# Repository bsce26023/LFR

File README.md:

# Autonomous Line Following Robot

I designed a LFR from scratch including the PCBs for main board and a custom sensor array. I designed this because I saw a friend of mine going into robotics competetions, so I also wanted to participate in them but I didn't have a robot that I could take to those competetions, so I finally built one myself. I chose STM32 because in some of those events there is a requirement that your robot should not have wireless connectivity, so the first thing that came into my mind was arduino uno but it is very slow and basic compared to other microcontrollers available on market then after some research I had two options Raspberry Pi Pico RP2040 or a STM32 Black Pill. raspberry pi pico had only 3 analog pins so I went with STM32.

To View the 3D assembly -->  [Assembly](https://cad.onshape.com/documents/d45a99fa843b34be3d8e85fd/w/9a64eb3e4a0355d274d4a744/e/07efc429ec569cf6f0da1301?renderMode=0&uiState=6a73ae4ff920c2919cbadd91)

||||
| :---: | :---: | :---: |
|  |  |  |

# Components

I've decided the components based on affordability, speed, availability and ease of use.
Starting with the micro controller I've selected **STM 32 BlackPill** and for motors I've selected **3000rpm 6v N20 motors with encoders** for fast speed  to drive these motors I've chosen **TB6612FNG motor driver** because it has low voltage drop and also it is way lighter than L298N. I've decided to use a 2S Li-Po battery which is about 7.4v which can power the motors with ease and to power STM32 I'd use a step down buck converter to convert these 7.4v into 5v so we don't damage the STM32 to charge the battery I'd use a 2S charger and for the sensors I've designed a custom sensor array.

##  PCB and Connections

To talk about the connections, I'd Start with the Power connections. The battery provides 7.4v which goes to VMOT pin of motor driver and buck converter. the buck converter then outputs 5v which goes to VSYS on Pico. Now we have 3 voltages. i.e. 7.4v, 5v and 3.3v. now the 3.3v goes to VCC and STBY pin of TB6612FNG and VCC pin on Sensor Array. 
Now lets talk about the Data and Logic Signals. The GPIO pins from 0 to 18 will be connected to sensor array and GPIO pins 19,20, 21, 22, 26, 27 will be connected to PWMA, AIN1, AIN2, PWMB, BIN1 and BIN2 respectively.
At the end the AO1,  AO2 and BO1, BO2 will be connected to left and right motors respectively.
[]

|Schematics|Tracks|
| :---: | :---: |
|  |  |

## Custom Built Sensor Array

I designed the schematics for the sensor array, it is the working principle is inspired from the QTR-16RC sensor array. I designed this because traditional sensors and sensor arrays look too uncool, so I had to design something that looked aesthetic and visually pleasing.

|Schematics|Tracks|
| :---: | :---: |
|  |  |

## Assembly & Firmware Guide

Because STM32 boards lack native USB bootloaders out-of-the-box like standard Arduino boards, flashing firmware requires a specific procedure using either an **ST-LINK V2 programmer** or the **built-in UART system memory bootloader**. 

### Step 1: Mechanical & Electrical Assembly
1. **Chassis & Motors:** Secure the DC gear motors to the mechanical chassis frame and attach the wheels.
2. **PCB Mounting:** Mount the fabricated PCB securely onto the chassis using standoffs.
3. **Wiring Connections:**
   * Connect the motor output leads from the gear motors to the motor driver output terminals (`M1`, `M2`).
   * Connect the IR sensor array to the designated analog/digital input header pins on the PCB.
   * Wire the power distribution, ensuring proper fusing and a stable common ground between the logic circuitry and motor drivers.

### Step 2: Setting Up the Development Environment
1. Install **Visual Studio Code** with the **PlatformIO IDE** extension (recommended for STM32 development) or **Arduino IDE** with the STMSS/STM32 Cores by STMicroelectronics installed via the Board Manager.
2. Clone or download this repository to your local machine.

### Step 3: Connecting the Programmer (ST-LINK V2 Method)
To flash code to an STM32 board, wire an external **ST-LINK V2 programmer** to the board's SWD pins:

| ST-LINK V2 Pin | STM32 Target Pin | Function |
| :--- | :--- | :--- |
| **3.3V** | **3.3V** | Power Supply |
| **GND** | **GND** | Common Ground |
| **SWDIO** | **PA13 (DIO)** | Serial Wire Data |
| **SWCLK** | **PA14 (CLK)** | Serial Wire Clock |

*Note: Ensure the target board is powered either via the ST-LINK's 3.3V pin (if current draw is low) or via an independent battery/bench supply.*

### Step 4: Uploading the Firmware
1. Open the project workspace in your IDE.
2. Verify that your `platformio.ini` or Arduino board settings match your exact STM32 part number (e.g., `stm32f103c8`).
3. Build/compile the project to check for syntax or dependency errors.
4. Initiate the upload command:
   * **In PlatformIO:** Click the **Upload** arrow icon (PlatformIO will automatically invoke OpenOCD and interface with your ST-LINK).
   * **In Arduino IDE:** Select **ST-LINK** under *Tools > Programmer*, then click **Upload**.
5. Once the upload finishes successfully, disconnect the programmer (or keep it connected for serial debugging via UART if configured), power cycle the robot, and place it on the test track.

# Bill of Materials (BOM)

| Name | Purpose | Quantity | Total Cost (USD) | Link | Distributor |
| --- | --- | --- | --- | --- | --- |
| PCB | PCB | 2 | 17 | https://cart.jlcpcb.com/shopcart/cart/ | JLCPCB |
| Mounting Brackets | Mounting motors | 1 | 3 | https://a.aliexpress.com/_c41oltrB | AliExpress |
| N20 Wheels | Wheels for Motors | 4 | 10 | https://a.aliexpress.com/_c3mDdjNx | Ali Express |
| Caster Wheels | Caster wheels | 2 | 4 | https://a.aliexpress.com/_c2yFCmMd | AliExpress |
| Slide Switch | Power Switch | 1 | 2 | https://a.aliexpress.com/_c3g6KmzX | AliExpress |
| TB6612FNG | Motor Driver | 1 | 4 | https://a.aliexpress.com/_c3bzgEgz | AliExpress |
| N20 Motors | Motors with Encoders | 4 | 25 | https://a.aliexpress.com/_c39Rykzn | AliExpress |
| Capacitor | Capacitance | 1 | 3 | https://a.aliexpress.com/_c3Ig4r1X | Aliexpress |
| Resistors | Resistance | 2 | 5 | https://a.aliexpress.com/_c3G1MsVL | Aliexpress |
| Limit switch | Bump sensor | 1 | 2.5 | https://a.aliexpress.com/_c3uz2Isv | Aliexpress |
| Ultrasonic sensor | Measures distance | 1 | 6 | https://a.aliexpress.com/_c35Zat1R | Aliexpress |
| TCRT5000 | Sensor | 1 | 7 | https://a.aliexpress.com/_c3RbgmiN | Aliexpress |
| Header pins | Soldering on pcb | 2 | 4 | https://a.aliexpress.com/_c4B0APx7 | Aliexpress |
| Mp1584 | Buck converter | 1 | 4.5 | https://a.aliexpress.com/_c4qnSguh | Aliexpress |
| Charging module | For charging battery | 1 | 2 | https://a.aliexpress.com/_c3Dtj3BL | Aliexpress |
| STM32 | Microcontroller | 1 | 6 | https://a.aliexpress.com/_c3GJD5FF | Aliexpress |
| Soldering Iron | For Soldering | 1 | 15 | https://epro.pk/product/soldering-iron-station-adjustable-temperature-esd-safe-kada-936-in-pakistan/ | Epro |
| Customs | - | - | 60 | - | AliExpress |
| Shipping | - | - | 20 | - | JLCPCB |
|  |  |  |  |  |  |
| Total | - | - | 200 | - | - |

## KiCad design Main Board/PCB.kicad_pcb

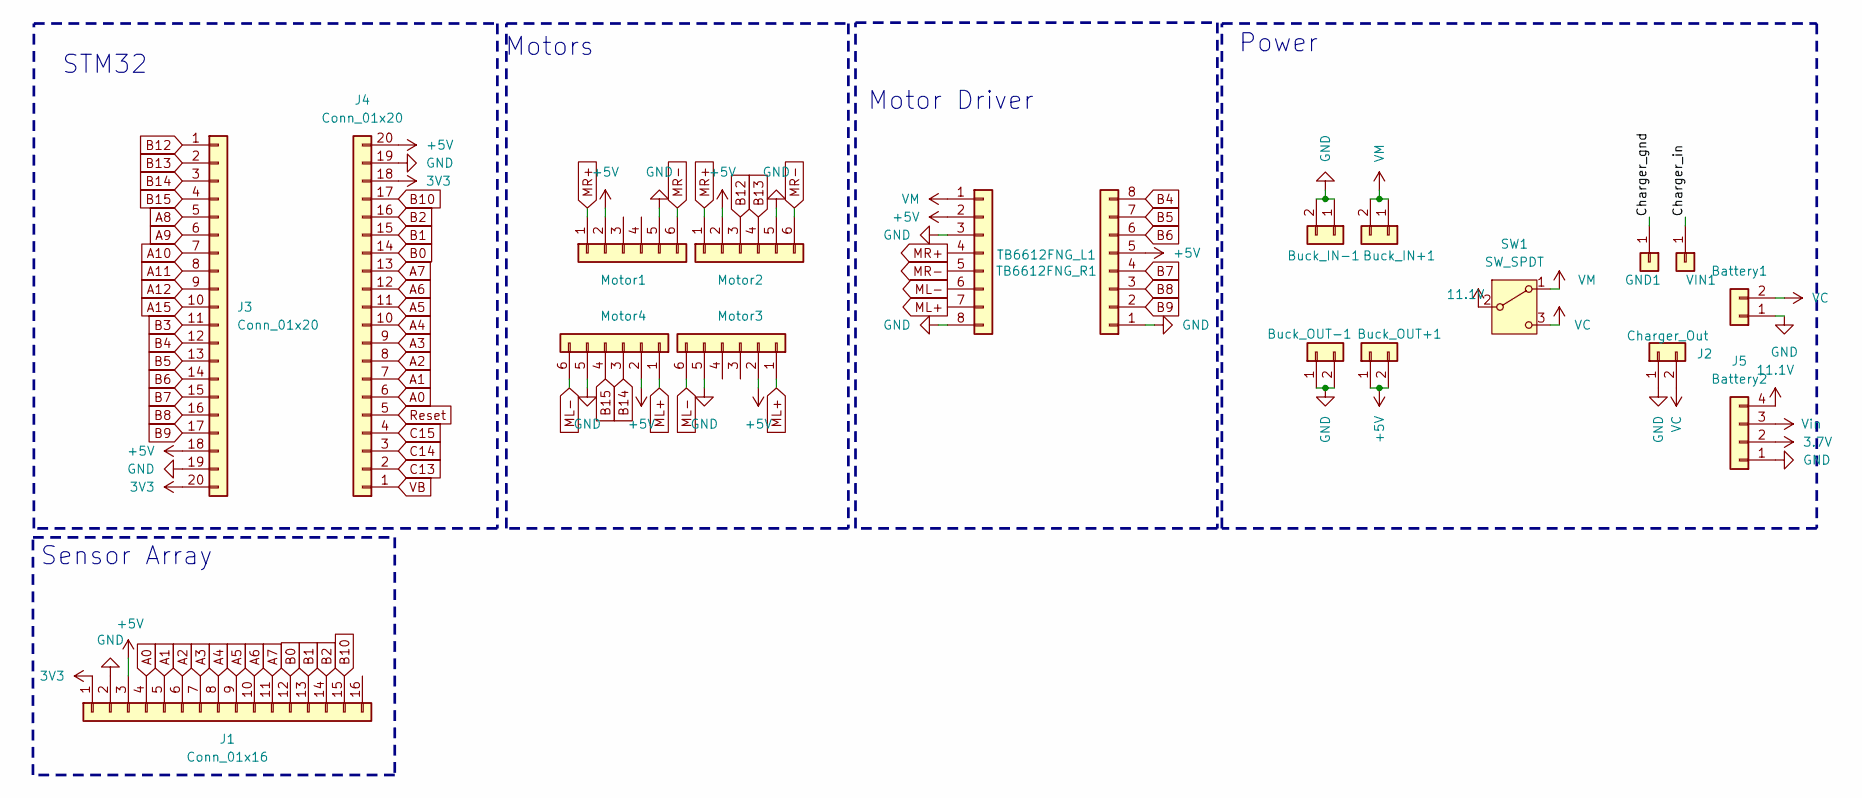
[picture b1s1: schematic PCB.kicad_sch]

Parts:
Battery1: Conn_01x02; AMASS_XT60-M_1x02_P7.20mm_Vertical
Buck_IN+1: Conn_01x02; PinSocket_1x02_P2.54mm_Vertical
Buck_IN-1: Conn_01x02; PinSocket_1x02_P2.54mm_Vertical
Buck_OUT+1: Conn_01x02; PinSocket_1x02_P2.54mm_Vertical
Buck_OUT-1: Conn_01x02; PinSocket_1x02_P2.54mm_Vertical
GND1: Conn_01x01; PinSocket_1x01_P2.54mm_Vertical
J1: Conn_01x16; PinHeader_1x16_P2.54mm_Vertical
J2: Charger_Out; PinSocket_1x02_P2.54mm_Vertical
J3, J4: Conn_01x20; PinSocket_1x20_P2.54mm_Vertical
J5: Battery2; JST_XH_B4B-XH-A_1x04_P2.50mm_Vertical
Motor1, Motor2, Motor3, Motor4: Conn_01x06; PinSocket_1x06_P2.54mm_Vertical
SW1: SW_SPDT; SW_Slide_SP3T_Straight_CK_OS103012MU1QP1
TB6612FNG_L1, TB6612FNG_R1: Conn_01x08; PinHeader_1x08_P2.54mm_Vertical
VIN1: Conn_01x01; PinHeader_1x01_P2.54mm_Vertical

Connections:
3.7V: J5.2
3V3: J1.1, J3.20, J4.18
+5V: Buck_OUT+1.1, Buck_OUT+1.2, J1.3, J3.18, J4.20, Motor1.2, Motor2.2, Motor3.2, Motor4.2, TB6612FNG_L1.2, TB6612FNG_R1.5
/Charger_gnd: GND1.1
/Charger_in: VIN1.1
A0: J1.4, J4.6
A1: J1.5, J4.7
A2: J1.6, J4.8
A3: J1.7, J4.9
A4: J1.8, J4.10
A5: J1.9, J4.11
A6: J1.10, J4.12
A7: J1.11, J4.13
A8: J3.5
A9: J3.6
A10: J3.7
A11: J3.8
A12: J3.9
A15: J3.10
B0: J1.12, J4.14
B1: J1.13, J4.15
B2: J1.14, J4.16
B3: J3.11
B4: J3.12, TB6612FNG_R1.8
B5: J3.13, TB6612FNG_R1.7
B6: J3.14, TB6612FNG_R1.6
B7: J3.15, TB6612FNG_R1.4
B8: J3.16, TB6612FNG_R1.3
B9: J3.17, TB6612FNG_R1.2
B10: J1.15, J4.17
B12: J3.1, Motor2.3
B13: J3.2, Motor2.4
B14: J3.3, Motor4.3
B15: J3.4, Motor4.4
C13: J4.2
C14: J4.3
C15: J4.4
GND: Battery1.1, Buck_IN-1.1, Buck_IN-1.2, Buck_OUT-1.1, Buck_OUT-1.2, J1.2, J2.1, J3.19, J4.19, J5.1, Motor1.5, Motor2.5, Motor3.5, Motor4.5, TB6612FNG_L1.3, TB6612FNG_L1.8, TB6612FNG_R1.1
ML+: Motor3.1, Motor4.1, TB6612FNG_L1.7
ML-: Motor3.6, Motor4.6, TB6612FNG_L1.6
MR+: Motor1.1, Motor2.1, TB6612FNG_L1.4
MR-: Motor1.6, Motor2.6, TB6612FNG_L1.5
Reset: J4.5
VB: J4.1
VM: Buck_IN+1.1, Buck_IN+1.2, SW1.1 (A), TB6612FNG_L1.1
Vin: J5.3

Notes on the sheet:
Power
Motor Driver
STM32
Motors
Sensor Array

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
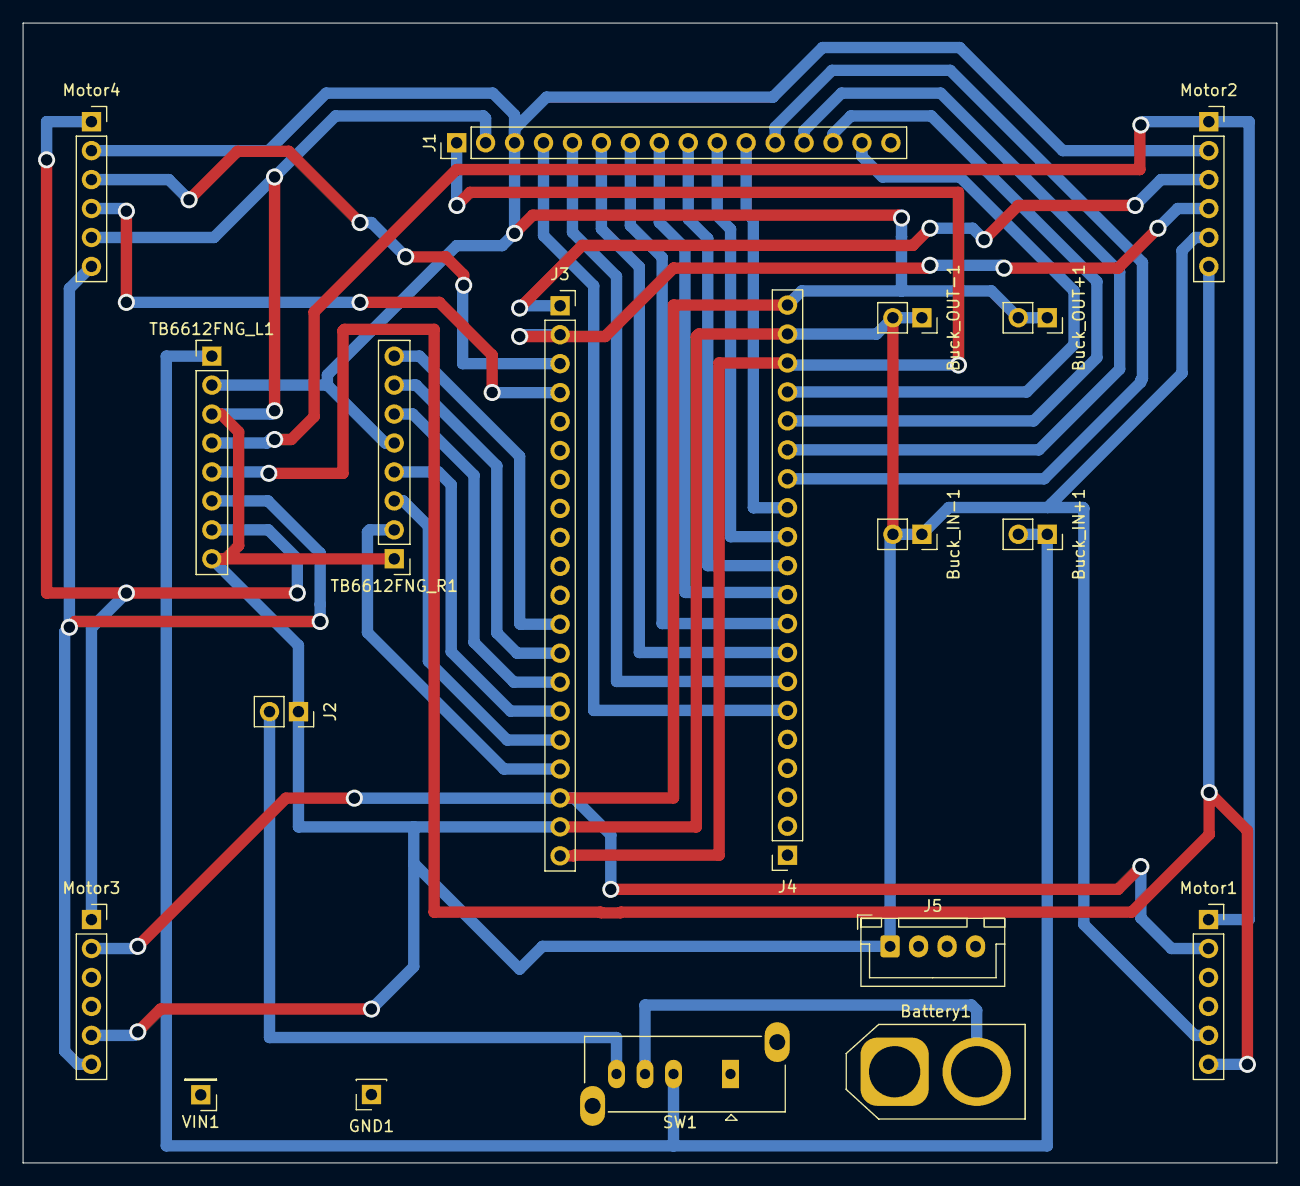
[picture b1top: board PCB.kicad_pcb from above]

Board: 2 copper layers, 110.0 x 100.0 mm, 19 parts (0 on the bottom side), 32 nets.

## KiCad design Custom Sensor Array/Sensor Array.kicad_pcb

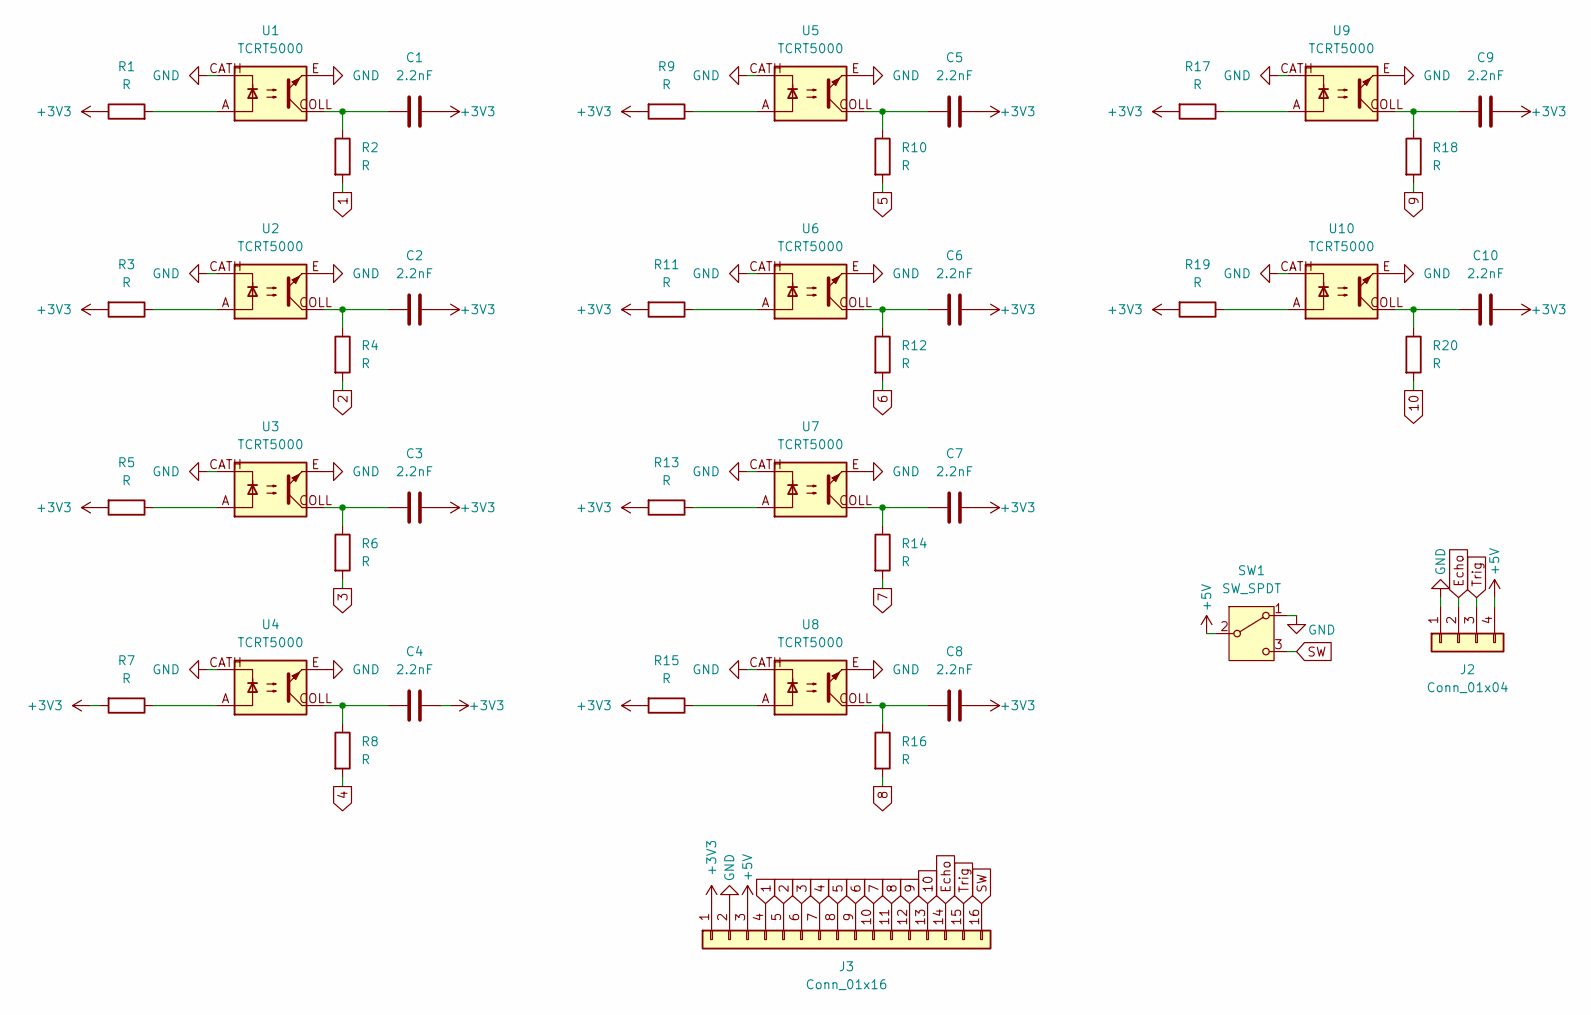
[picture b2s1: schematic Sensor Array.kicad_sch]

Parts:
C1, C2, C3, C4, C5, C6, C7, C8, C9, C10: 2.2nF; C_0805_2012Metric_Pad1.18x1.45mm_HandSolder
J2: Conn_01x04; PinHeader_1x04_P2.54mm_Vertical
J3: Conn_01x16; PinHeader_1x16_P2.54mm_Vertical
R1, R2, R3, R4, R5, R6, R7, R8, R9, R10, R11, R12, R13, R14, R15, R16, R17, R18, R19, R20: R; R_0805_2012Metric_Pad1.20x1.40mm_HandSolder
SW1: SW_SPDT; SW_Slide_SPDT_Straight_CK_OS102011MS2Q
U1, U2, U3, U4, U5, U6, U7, U8, U9, U10: TCRT5000; tcrt5000

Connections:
1: J3.4, R2.2
2: J3.5, R4.2
3: J3.6, R6.2
4: J3.7, R8.2
5: J3.8, R10.2
6: J3.9, R12.2
7: J3.10, R14.2
8: J3.11, R16.2
9: J3.12, R18.2
10: J3.13, R20.2
+3V3: C1.2, C2.2, C3.2, C4.2, C5.2, C6.2, C7.2, C8.2, C9.2, C10.2, J3.1, R1.1, R3.2, R5.2, R7.2, R9.2, R11.2, R13.2, R15.2, R17.2, R19.2
+5V: J2.4, J3.3, SW1.2 (B)
Echo: J2.2, J3.14
GND: J2.1, J3.2, SW1.1 (A), U1.CATH, U1.E, U2.CATH, U2.E, U3.CATH, U3.E, U4.CATH, U4.E, U5.CATH, U5.E, U6.CATH, U6.E, U7.CATH, U7.E, U8.CATH, U8.E, U9.CATH, U9.E, U10.CATH, U10.E
unnamed: C1.1, R2.1, U1.COLL
unnamed: C2.1, R4.1, U2.COLL
unnamed: C3.1, R6.1, U3.COLL
unnamed: C4.1, R8.1, U4.COLL
unnamed: C5.1, R10.1, U5.COLL
unnamed: C6.1, R12.1, U6.COLL
unnamed: C7.1, R14.1, U7.COLL
unnamed: C8.1, R16.1, U8.COLL
unnamed: C9.1, R18.1, U9.COLL
unnamed: C10.1, R20.1, U10.COLL
unnamed: R1.2, U1.A
unnamed: R3.1, U2.A
unnamed: R5.1, U3.A
unnamed: R7.1, U4.A
unnamed: R9.1, U5.A
unnamed: R11.1, U6.A
unnamed: R13.1, U7.A
unnamed: R15.1, U8.A
unnamed: R17.1, U9.A
unnamed: R19.1, U10.A
SW: J3.16, SW1.3 (C)
Trig: J2.3, J3.15

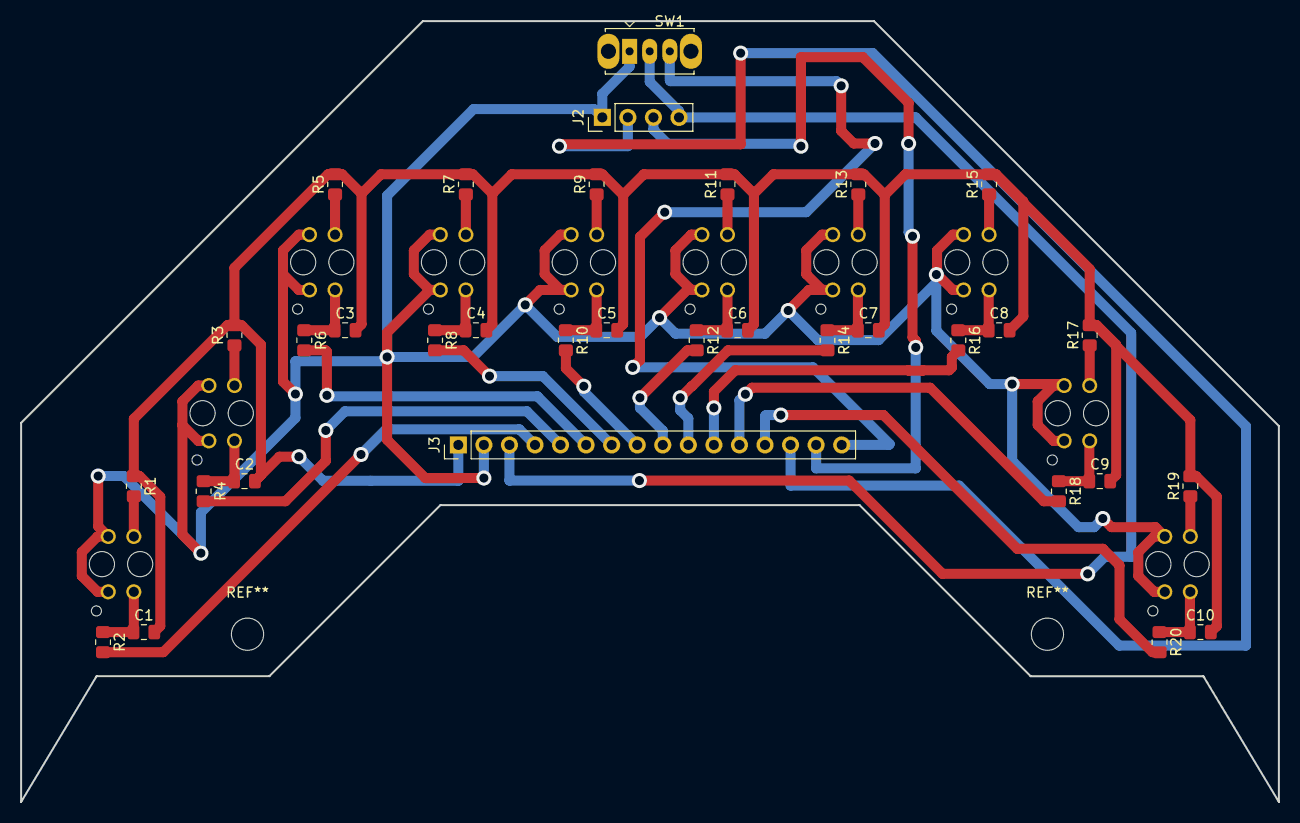
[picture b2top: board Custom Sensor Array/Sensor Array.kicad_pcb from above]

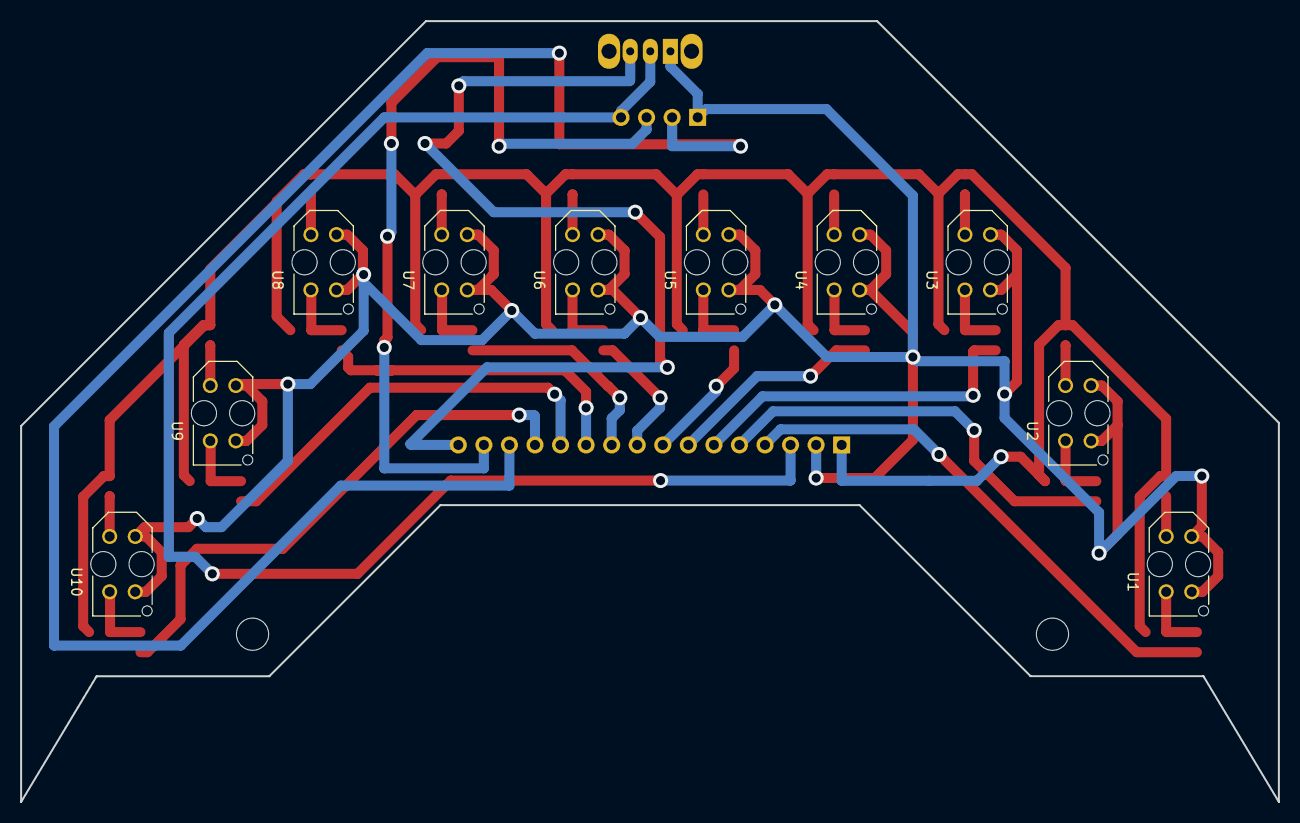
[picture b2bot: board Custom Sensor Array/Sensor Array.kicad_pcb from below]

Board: 2 copper layers, 125.0 x 77.6 mm, 43 parts (10 on the bottom side), 36 nets.

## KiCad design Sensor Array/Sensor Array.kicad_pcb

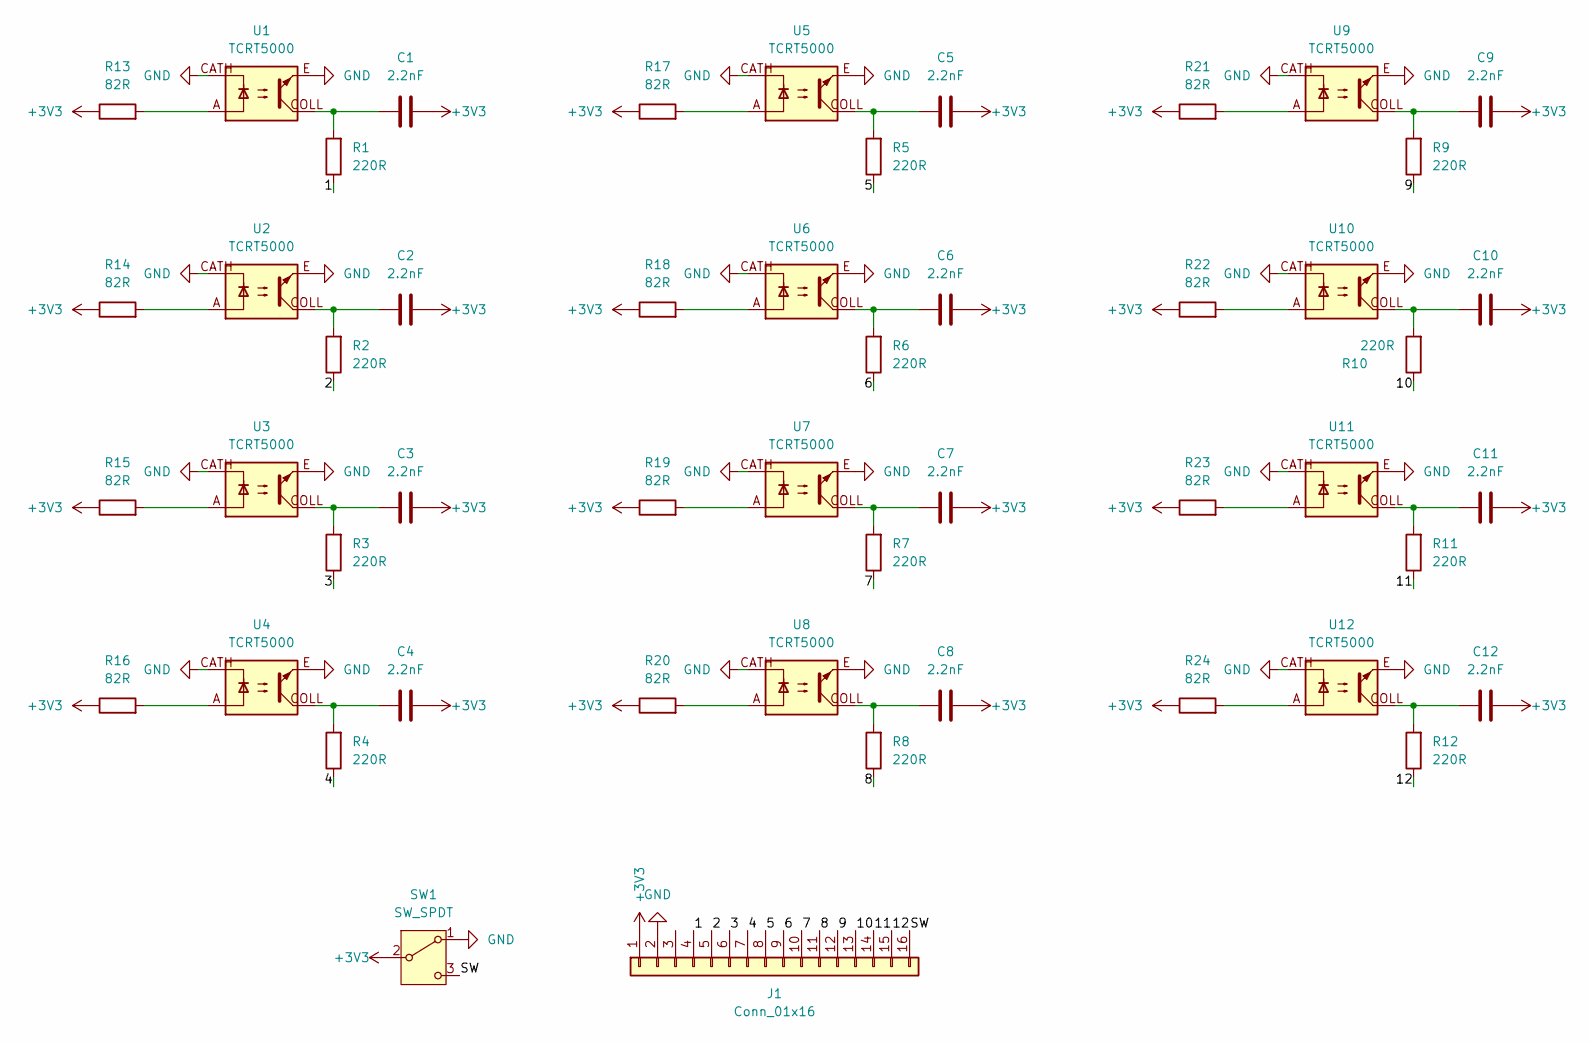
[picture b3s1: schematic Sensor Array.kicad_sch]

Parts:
C1, C2, C3, C4, C5, C6, C7, C8, C9, C10, C11, C12: 2.2nF; C_0805_2012Metric_Pad1.18x1.45mm_HandSolder
J1: Conn_01x16; PinHeader_1x16_P2.54mm_Vertical
R1, R2, R3, R4, R5, R6, R7, R8, R9, R10, R11, R12: 220R; R_0805_2012Metric_Pad1.20x1.40mm_HandSolder
R13, R14, R15, R16, R17, R18, R19, R20, R21, R22, R23, R24: 82R; R_0805_2012Metric_Pad1.20x1.40mm_HandSolder
SW1: SW_SPDT; SW_Slide_SPDT_Straight_CK_OS102011MS2Q
U1, U2, U3, U4, U5, U6, U7, U8, U9, U10, U11, U12: TCRT5000; tcrt5000

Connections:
+3V3: C1.2, C2.2, C3.2, C4.2, C5.2, C6.2, C7.2, C8.2, C9.2, C10.2, C11.2, C12.2, J1.1, R13.1, R14.1, R15.1, R16.1, R17.1, R18.1, R19.1, R20.1, R21.1, R22.1, R23.1, R24.1, SW1.2 (B)
/1: J1.4, R1.1
/2: J1.5, R2.1
/3: J1.6, R3.1
/4: J1.7, R4.1
/5: J1.8, R5.1
/6: J1.9, R6.1
/7: J1.10, R7.1
/8: J1.11, R8.1
/9: J1.12, R9.1
/10: J1.13, R10.1
/11: J1.14, R11.1
/12: J1.15, R12.1
/SW: J1.16, SW1.3 (C)
GND: J1.2, SW1.1 (A), U1.CATH, U1.E, U2.CATH, U2.E, U3.CATH, U3.E, U4.CATH, U4.E, U5.CATH, U5.E, U6.CATH, U6.E, U7.CATH, U7.E, U8.CATH, U8.E, U9.CATH, U9.E, U10.CATH, U10.E, U11.CATH, U11.E, U12.CATH, U12.E
unnamed: C1.1, R1.2, U1.COLL
unnamed: C2.1, R2.2, U2.COLL
unnamed: C3.1, R3.2, U3.COLL
unnamed: C4.1, R4.2, U4.COLL
unnamed: C5.1, R5.2, U5.COLL
unnamed: C6.1, R6.2, U6.COLL
unnamed: C7.1, R7.2, U7.COLL
unnamed: C8.1, R8.2, U8.COLL
unnamed: C9.1, R9.2, U9.COLL
unnamed: C10.1, R10.2, U10.COLL
unnamed: C11.1, R11.2, U11.COLL
unnamed: C12.1, R12.2, U12.COLL
unnamed: R13.2, U1.A
unnamed: R14.2, U2.A
unnamed: R15.2, U3.A
unnamed: R16.2, U4.A
unnamed: R17.2, U5.A
unnamed: R18.2, U6.A
unnamed: R19.2, U7.A
unnamed: R20.2, U8.A
unnamed: R21.2, U9.A
unnamed: R22.2, U10.A
unnamed: R23.2, U11.A
unnamed: R24.2, U12.A

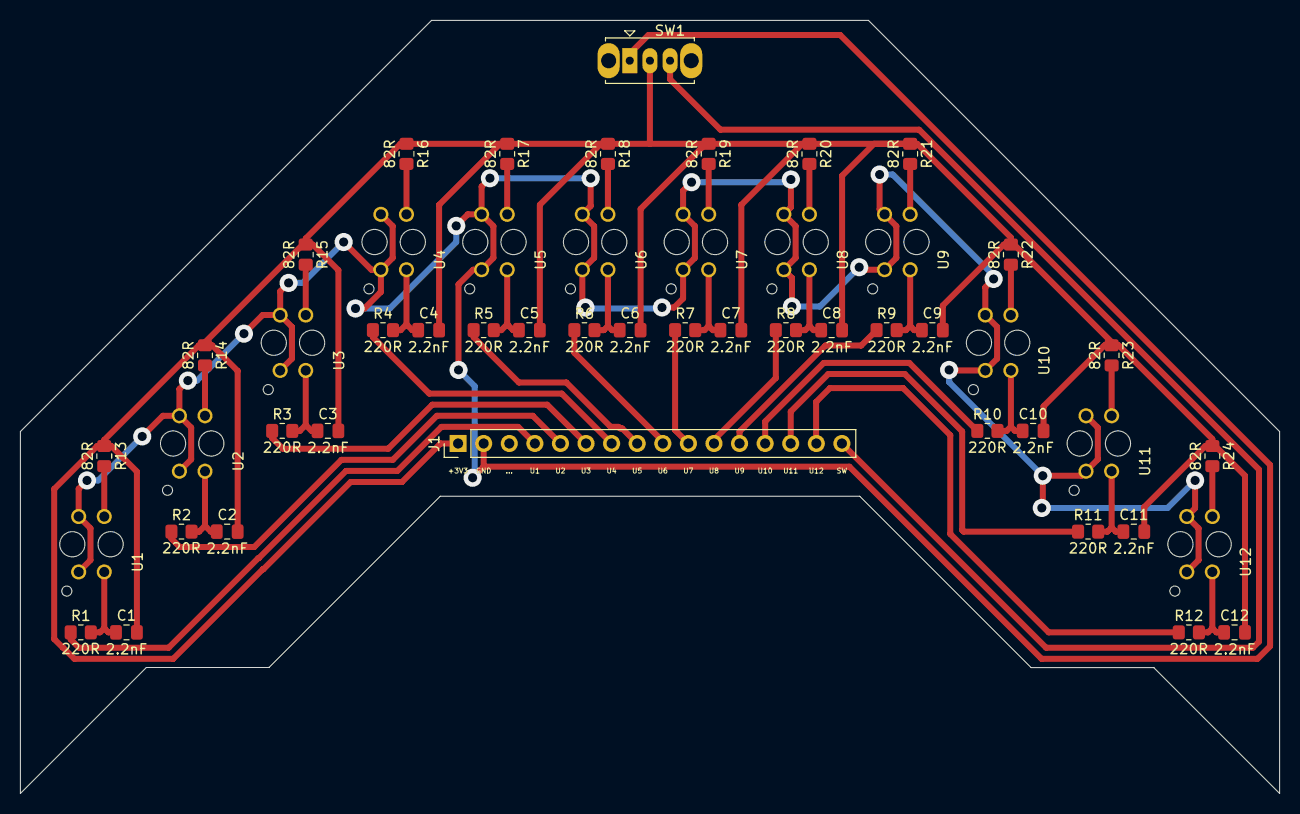
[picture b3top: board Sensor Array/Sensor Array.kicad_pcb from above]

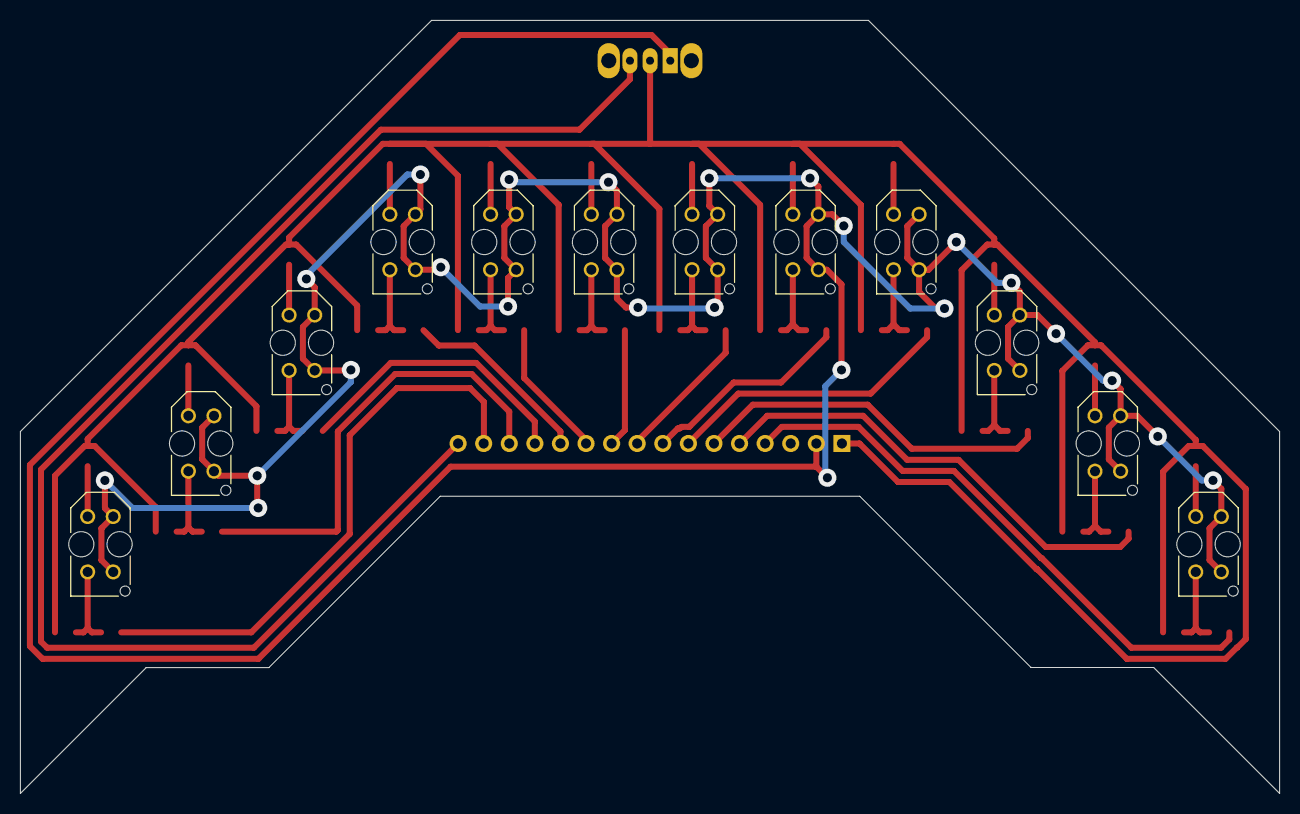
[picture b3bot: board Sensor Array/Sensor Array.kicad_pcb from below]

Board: 2 copper layers, 125.0 x 76.7 mm, 50 parts (12 on the bottom side), 39 nets.

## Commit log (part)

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2026-05-14 Sensor Array
2026-06-17 Schematics
2026-06-18 Sensor Array Finalized
2026-06-18 Step Files Exported
2026-06-20 3D files added
2026-06-20 Add initial README file
2026-06-20 Updated Readme, Added BOM
2026-06-20 Updated BOM
